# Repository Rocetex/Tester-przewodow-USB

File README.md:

# Tester przewodow USB
## Wstęp:
Jako projekt wstępnie wybrano tester przewodów USB. Wymagania przyjęte do tego projektu były następujące: stosunkowo niski koszt, prostota obsługi, kompaktowość i wszechstronność. Zdecydowano się, aby tester przeznaczony był dla przewodów USB type C - USB type C. Po podłączeniu przewodów do urządzenia  powinno ono podświetleniem poszczególnych diod ukazywać w jakim trybie może działać dany przewód, oraz możliwe uszkodzenia i cięcia budżetowe producenta w jego strukturze. 

## Założenia projektu:
* Możliwość testu 2 typów przewodów: USB A -> USB C oraz USB C -> USB C
* Dwa tryby częstotliwości pracy układu
* Kompaktowość urządzenia
* Niska cena
  
## Schemat i projekt układu
Wstępny zamysł projektu był następujący. Odpowiednio zaprojektowany system zegara CLK oparty o układ scalony NE555. Następnie sygnał ten przechodzi na 5 przerzutników typu JK działających w układzie licznika synchronicznego od 0 - 24, dzięki czemu możliwe było obsłużenie wszystkich 25 sygnałów pełnego złącza USB type C (a dokładniej 24 pinów sygnałowych oraz shielda). W ten sposób zaprojektowano układ licznika 5 bitowego. Sygnał z poszczególnych wyjść liczników trafia na dwa 4 bitowe dekodery połączone w odpowiedni sposób, zamiast na jeden dekoder 5 bitowy. Wynika to z faktu dostępności i ceny. Układ dwóch 4 bitowych dekoderów jest tańszy i łatwiej dostępny. Sygnał z poszczególnych wyjść dekoderów trafiał na odpowiednie mosfety typu P, a one po otrzymaniu sygnału załączeniowego (logiczne “0”) zaczynały przewodzić do odpowiedniego pinu złącza USB C. Następnie przez przewód sygnał trafiał na odpowiednie szeregowo połączone rezystory i diody, które zaczynały świecić, sygnalizująć działanie danego pinu.

## Instrukcja obsługi:
Płytkę należy zasilić napięciem 5V. 
Switch S1 odowiada za resetowanie układu.
Przełącznik S3 odpowiada za wybranie częstotliwości pracy układu
Przełącznik S4 odpowiada za wybranie trybu pracy:
1) USB typu A
2) USB typu C
Aby przetestować przewód USB A -> USB C:
- Podłączyć zasilanie do płytki
- Ustawić oczelowamą częstotliwość pracy układu
- Ustawić tryb pracy na USB A
- Wpiąć przewód z złącze USB A (oznaczone na płytce jako J3) oraz w wyjściowe złącze USB typu C (J2)
Aby przetestować przewód USB C -> USB C:
- Podłączyć zasilanie do płytki
- Ustawić oczelowamą częstotliwość pracy układu
- Ustawić tryb pracy na USB C
- Wpiąć przewód z złącze USB C (oznaczone na płytce jako J1) oraz w wyjściowe złącze USB typu C (J2)

## Błędy w konstrukcji płytki:
- Kondensator C3 należy przylutować równolegle do masy oraz do zwartych padów miejsca kondensatora
- Pomimo wykonania symulacji zauważono problem z zamykaniem się mosfetów, z tego powodu zaleca się użycie tranzystorów PNP oraz rezystorów na bramce 1k Ohm

## Prezentacja układu:

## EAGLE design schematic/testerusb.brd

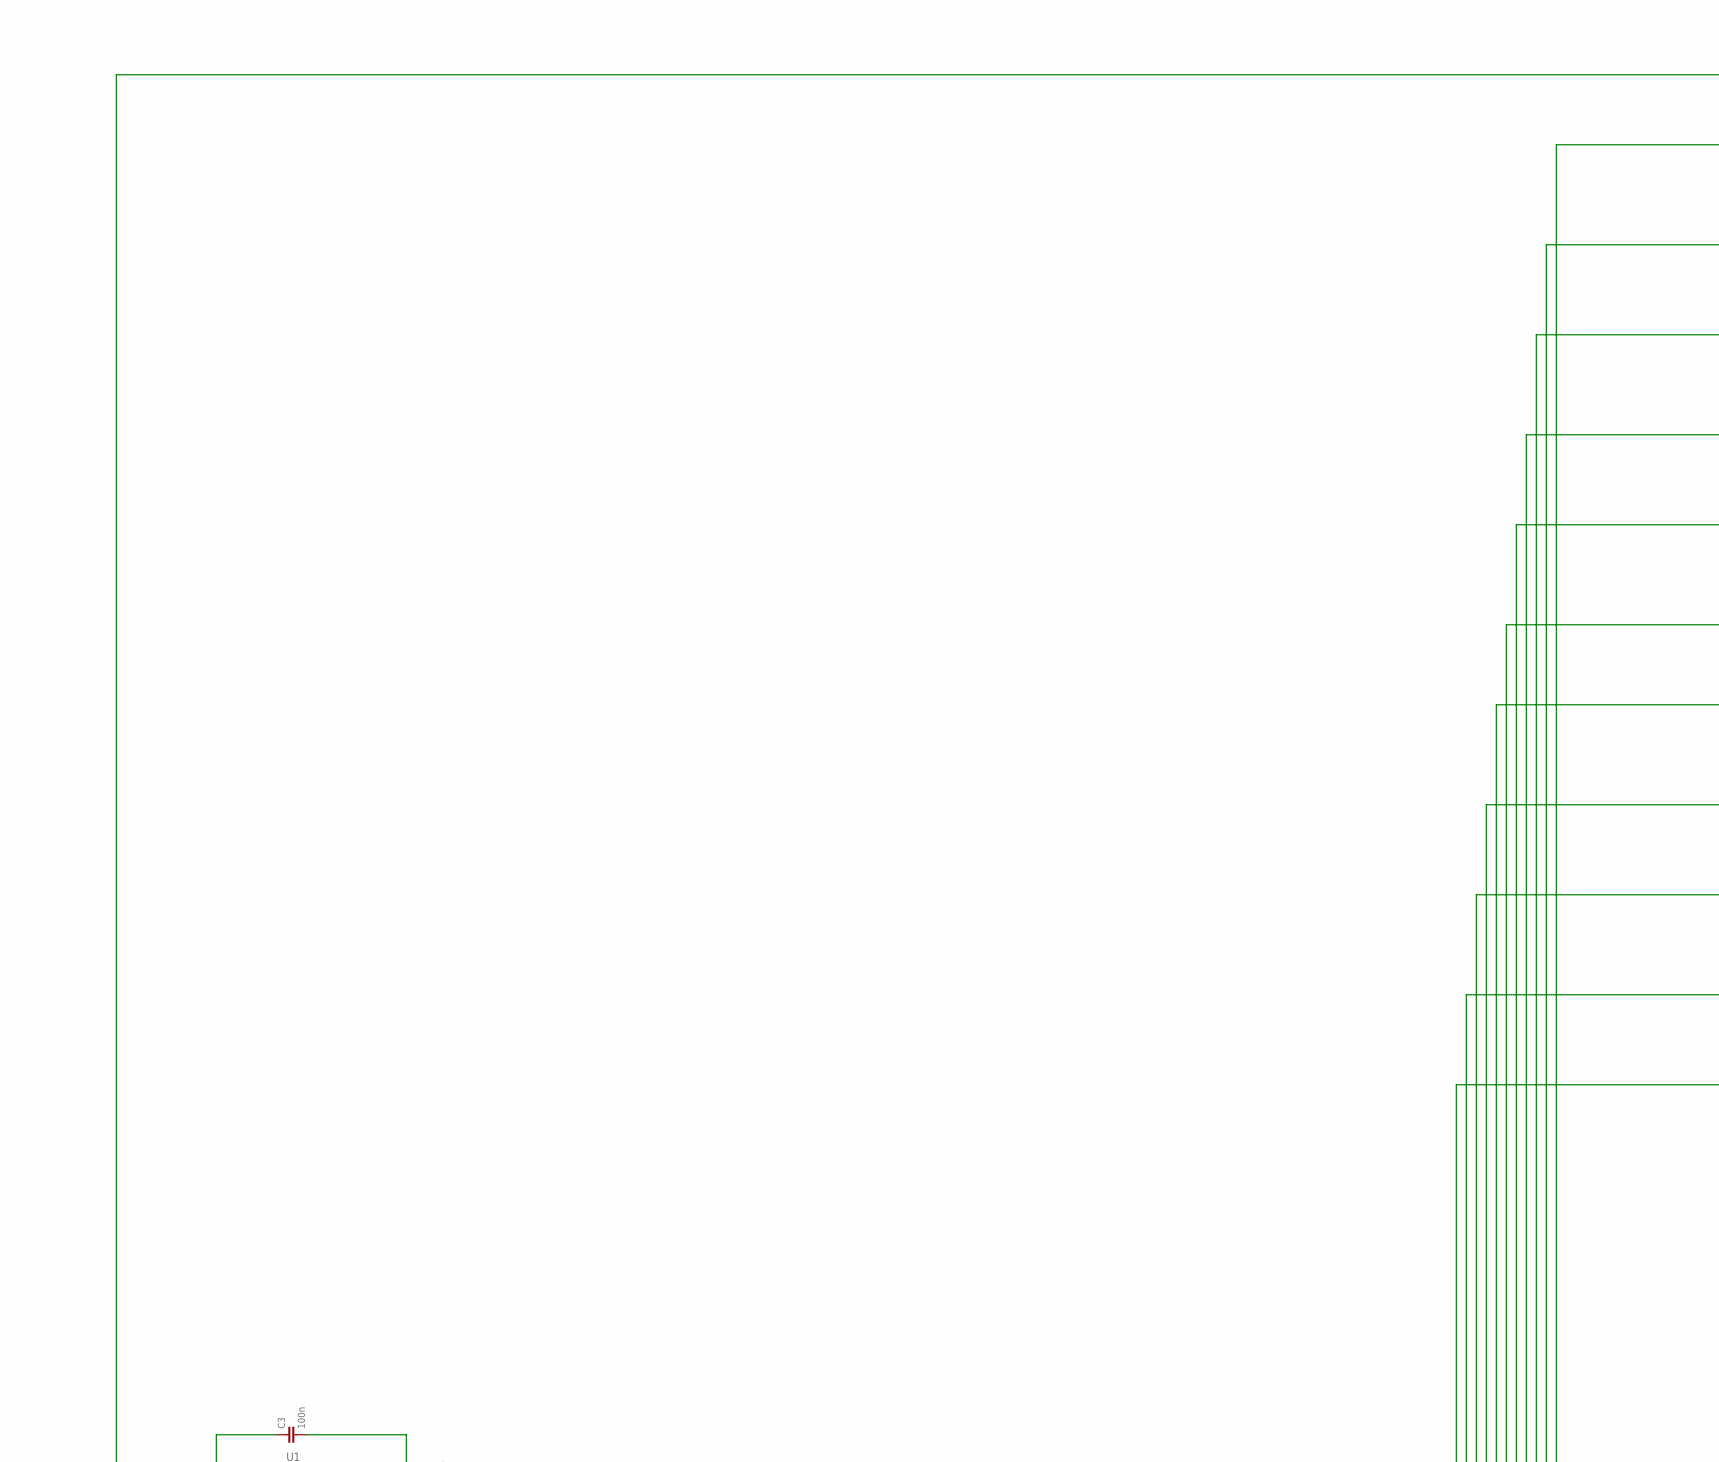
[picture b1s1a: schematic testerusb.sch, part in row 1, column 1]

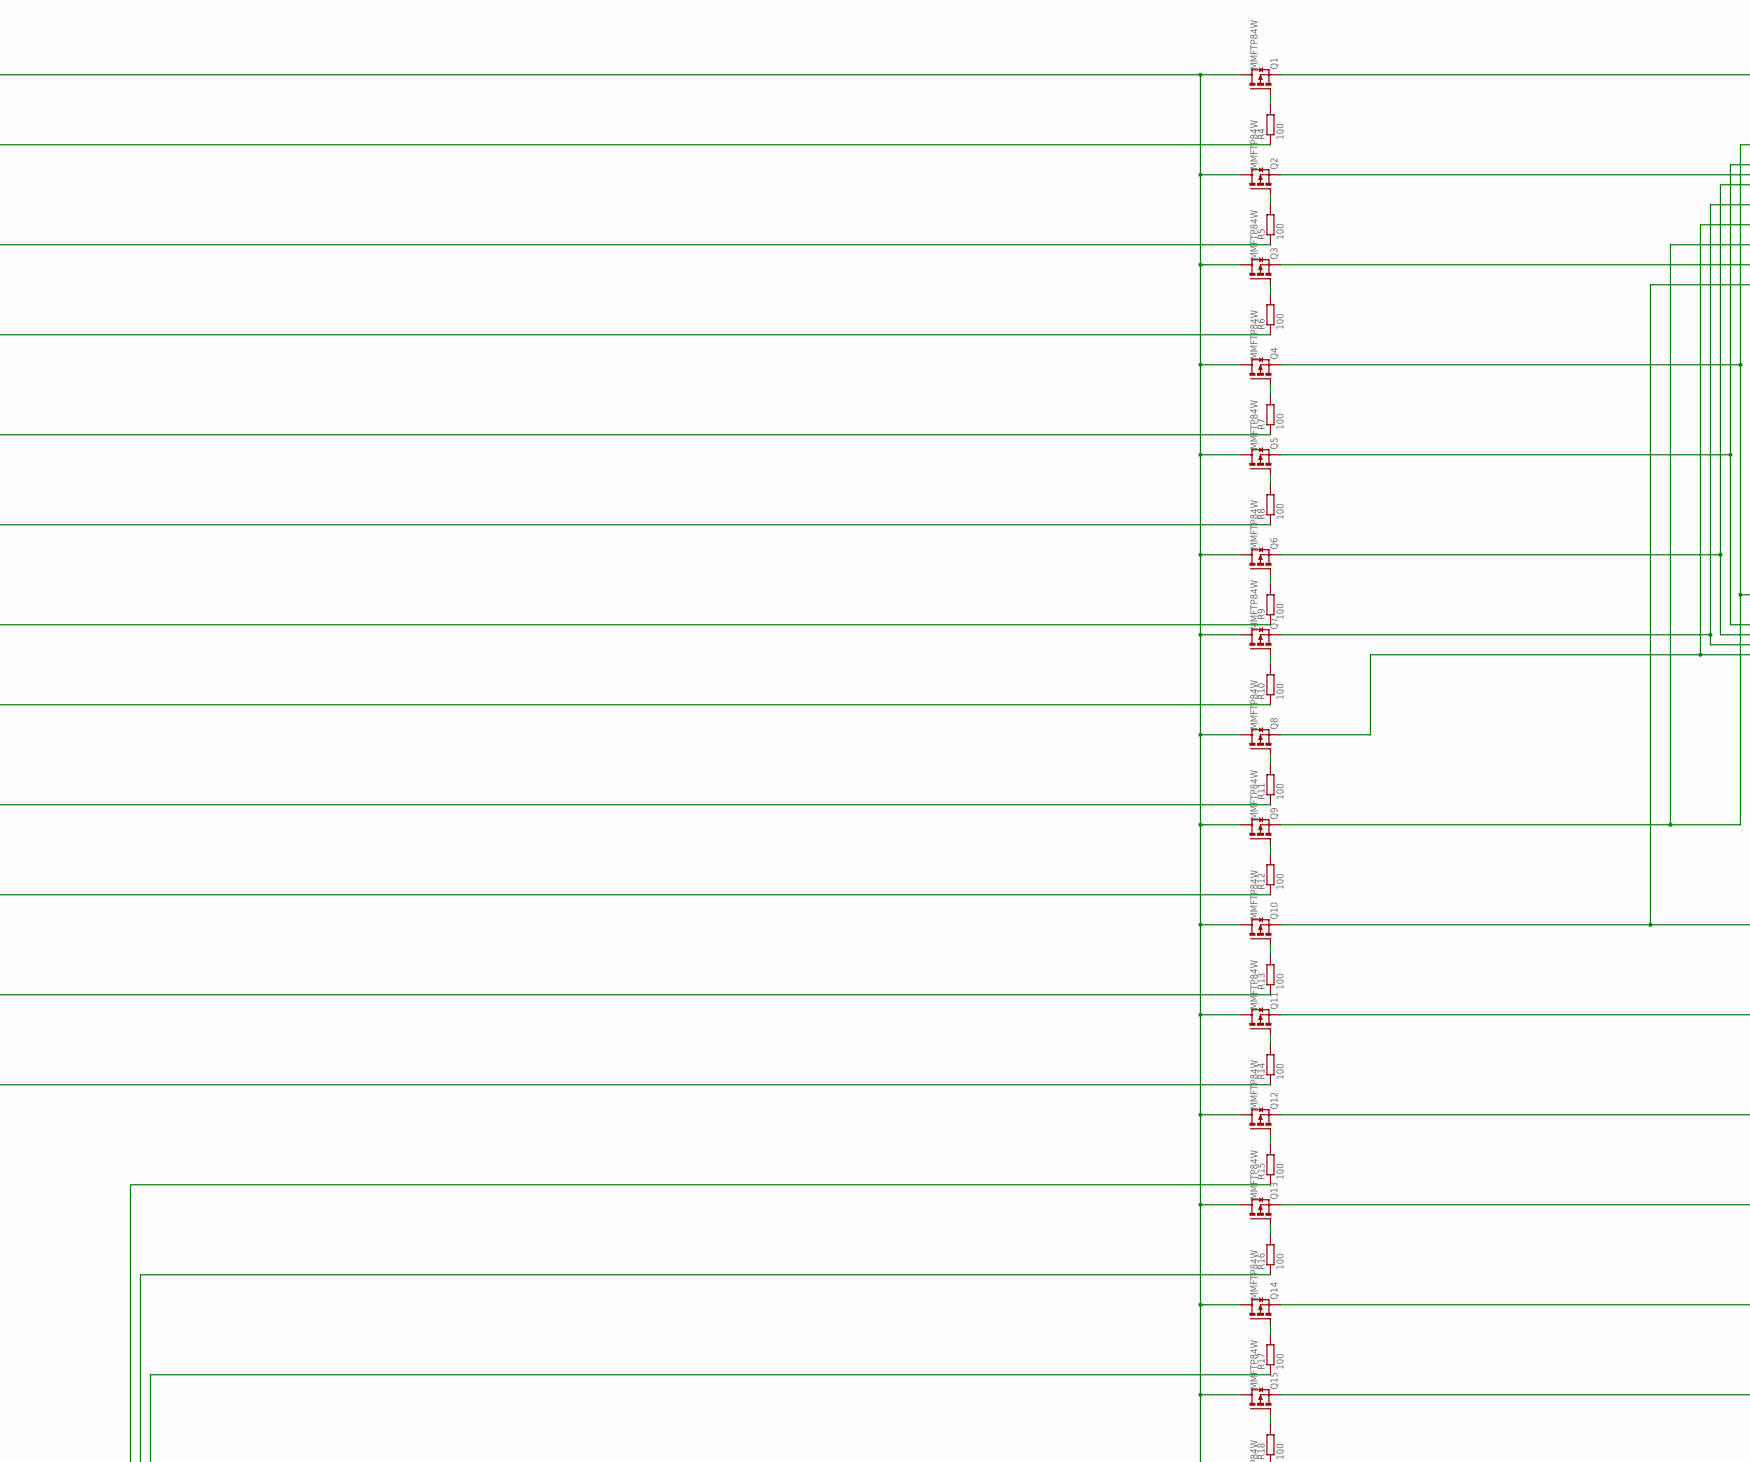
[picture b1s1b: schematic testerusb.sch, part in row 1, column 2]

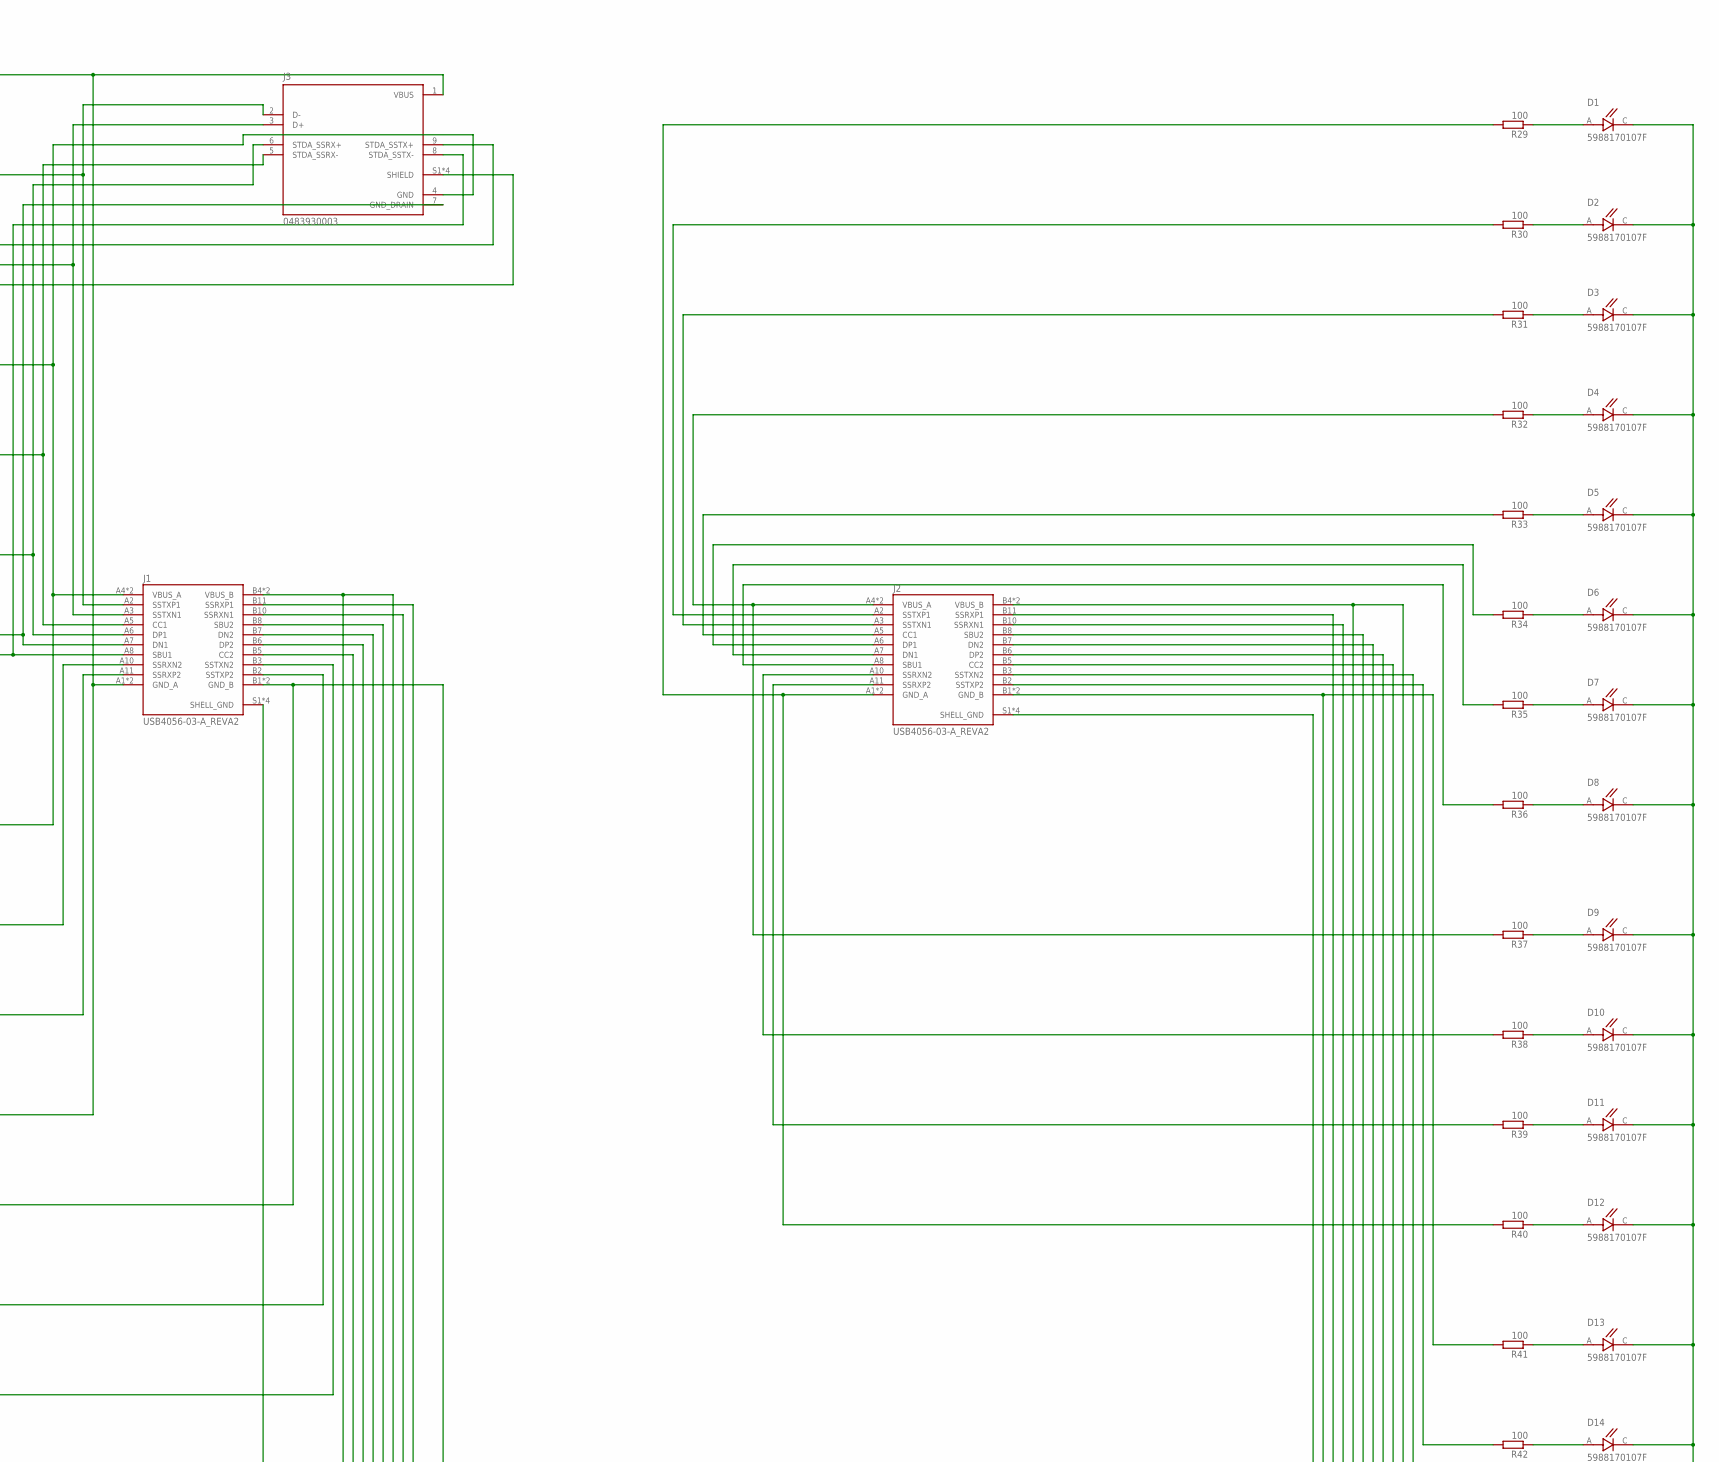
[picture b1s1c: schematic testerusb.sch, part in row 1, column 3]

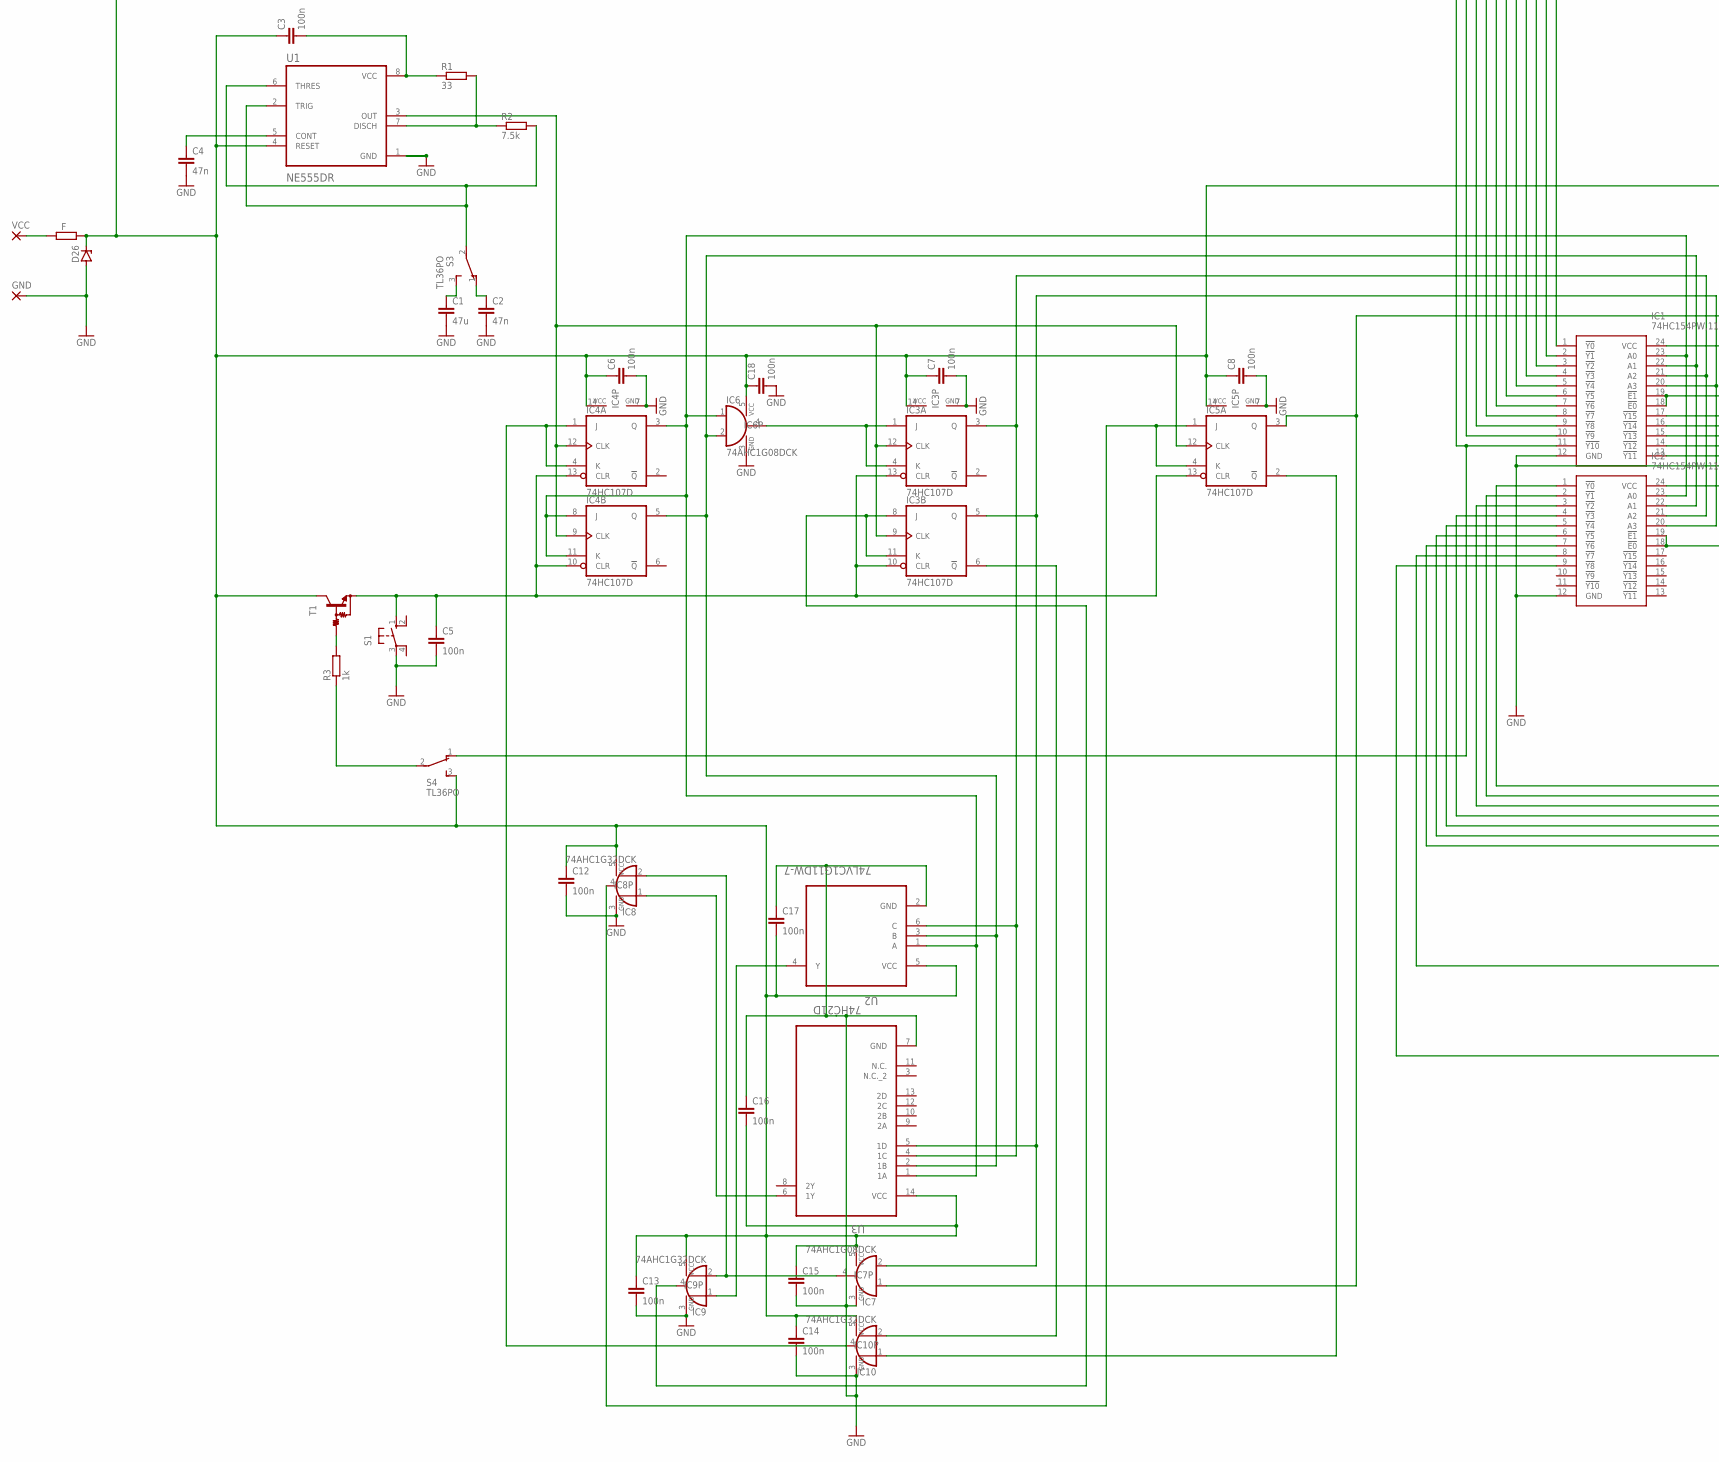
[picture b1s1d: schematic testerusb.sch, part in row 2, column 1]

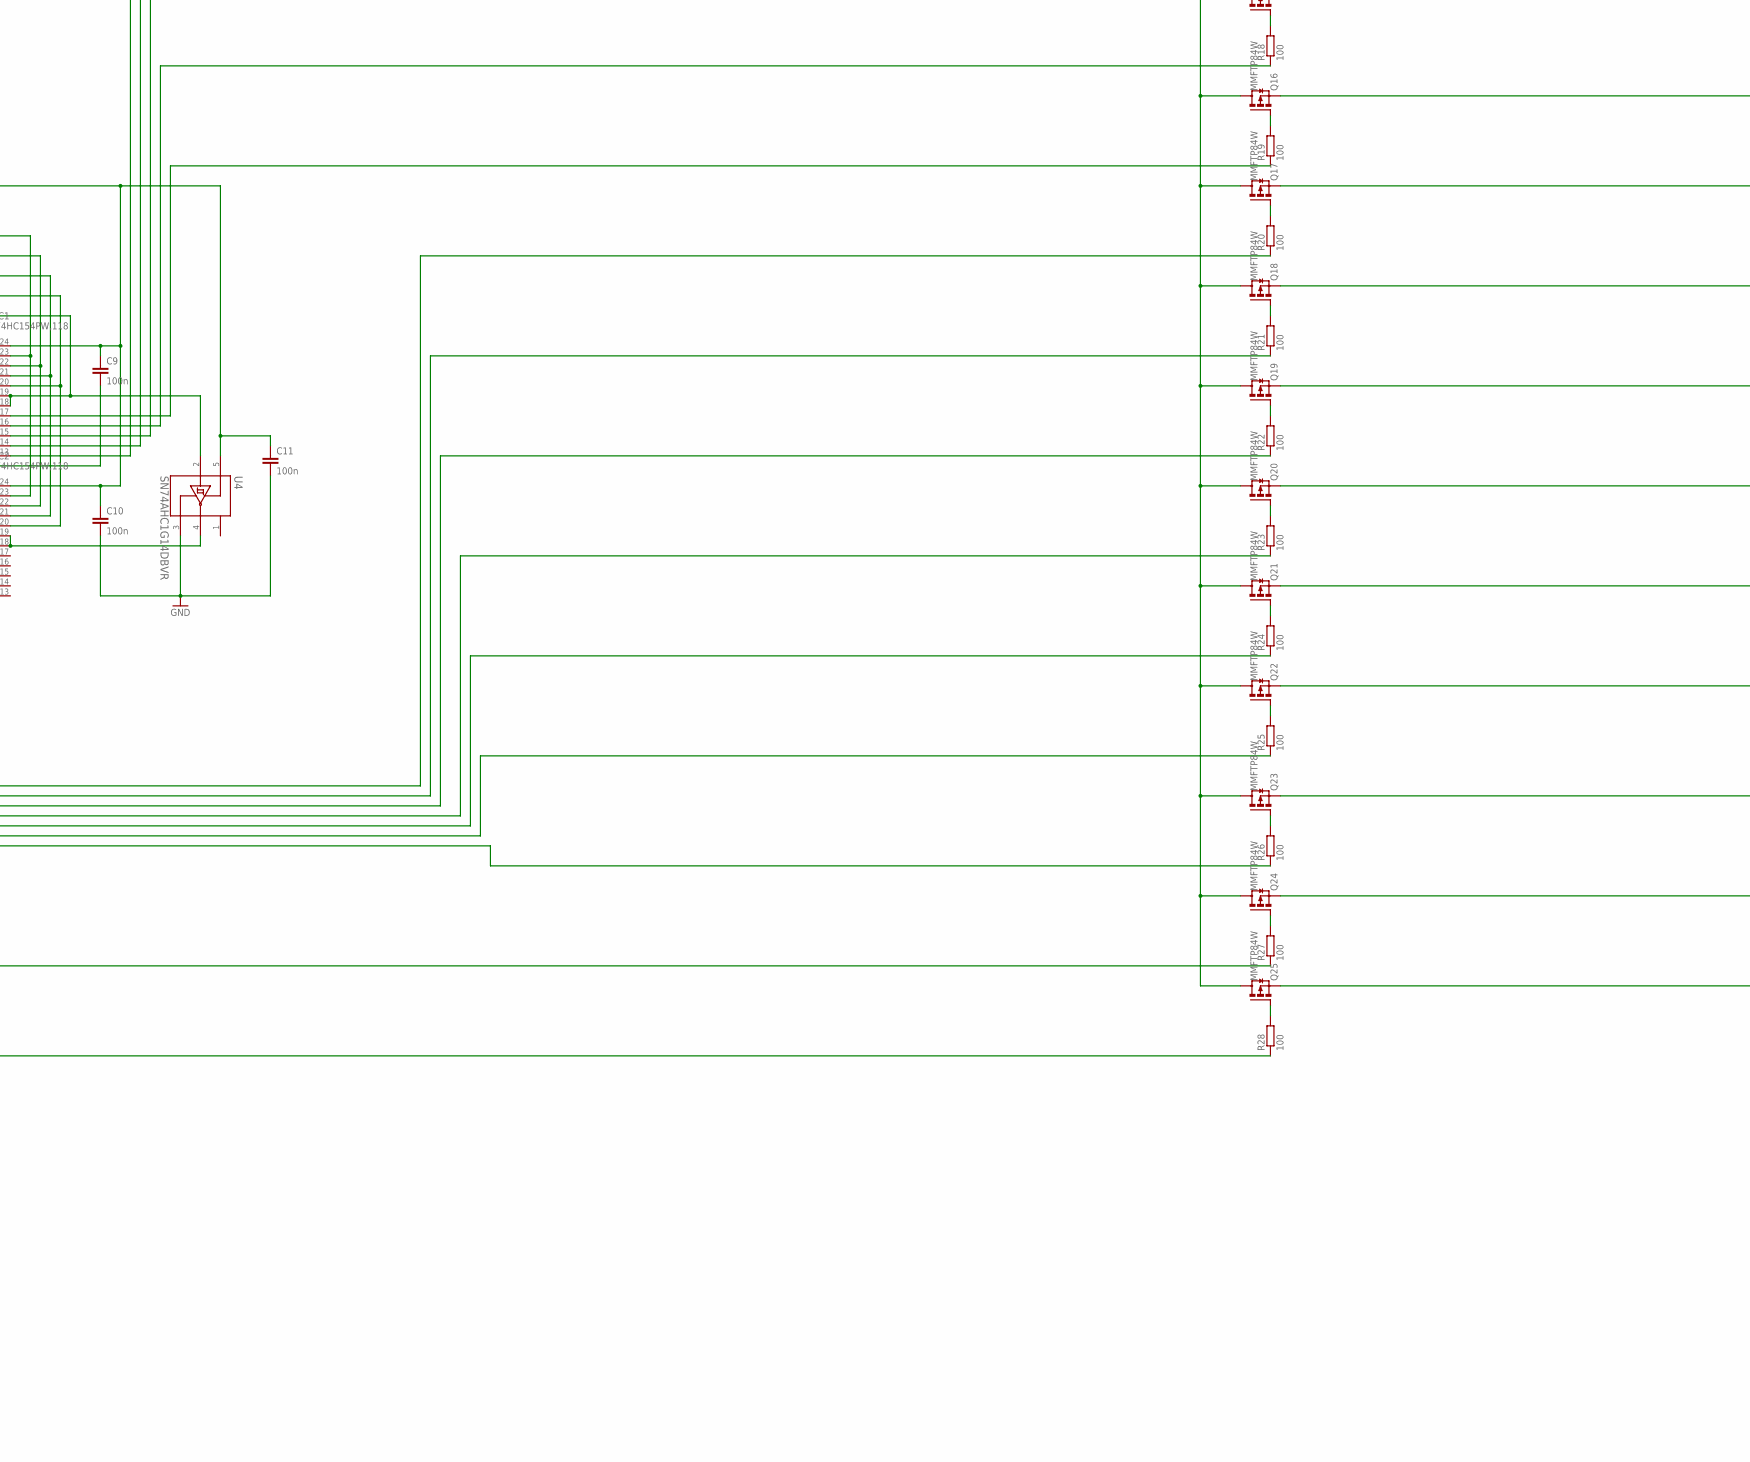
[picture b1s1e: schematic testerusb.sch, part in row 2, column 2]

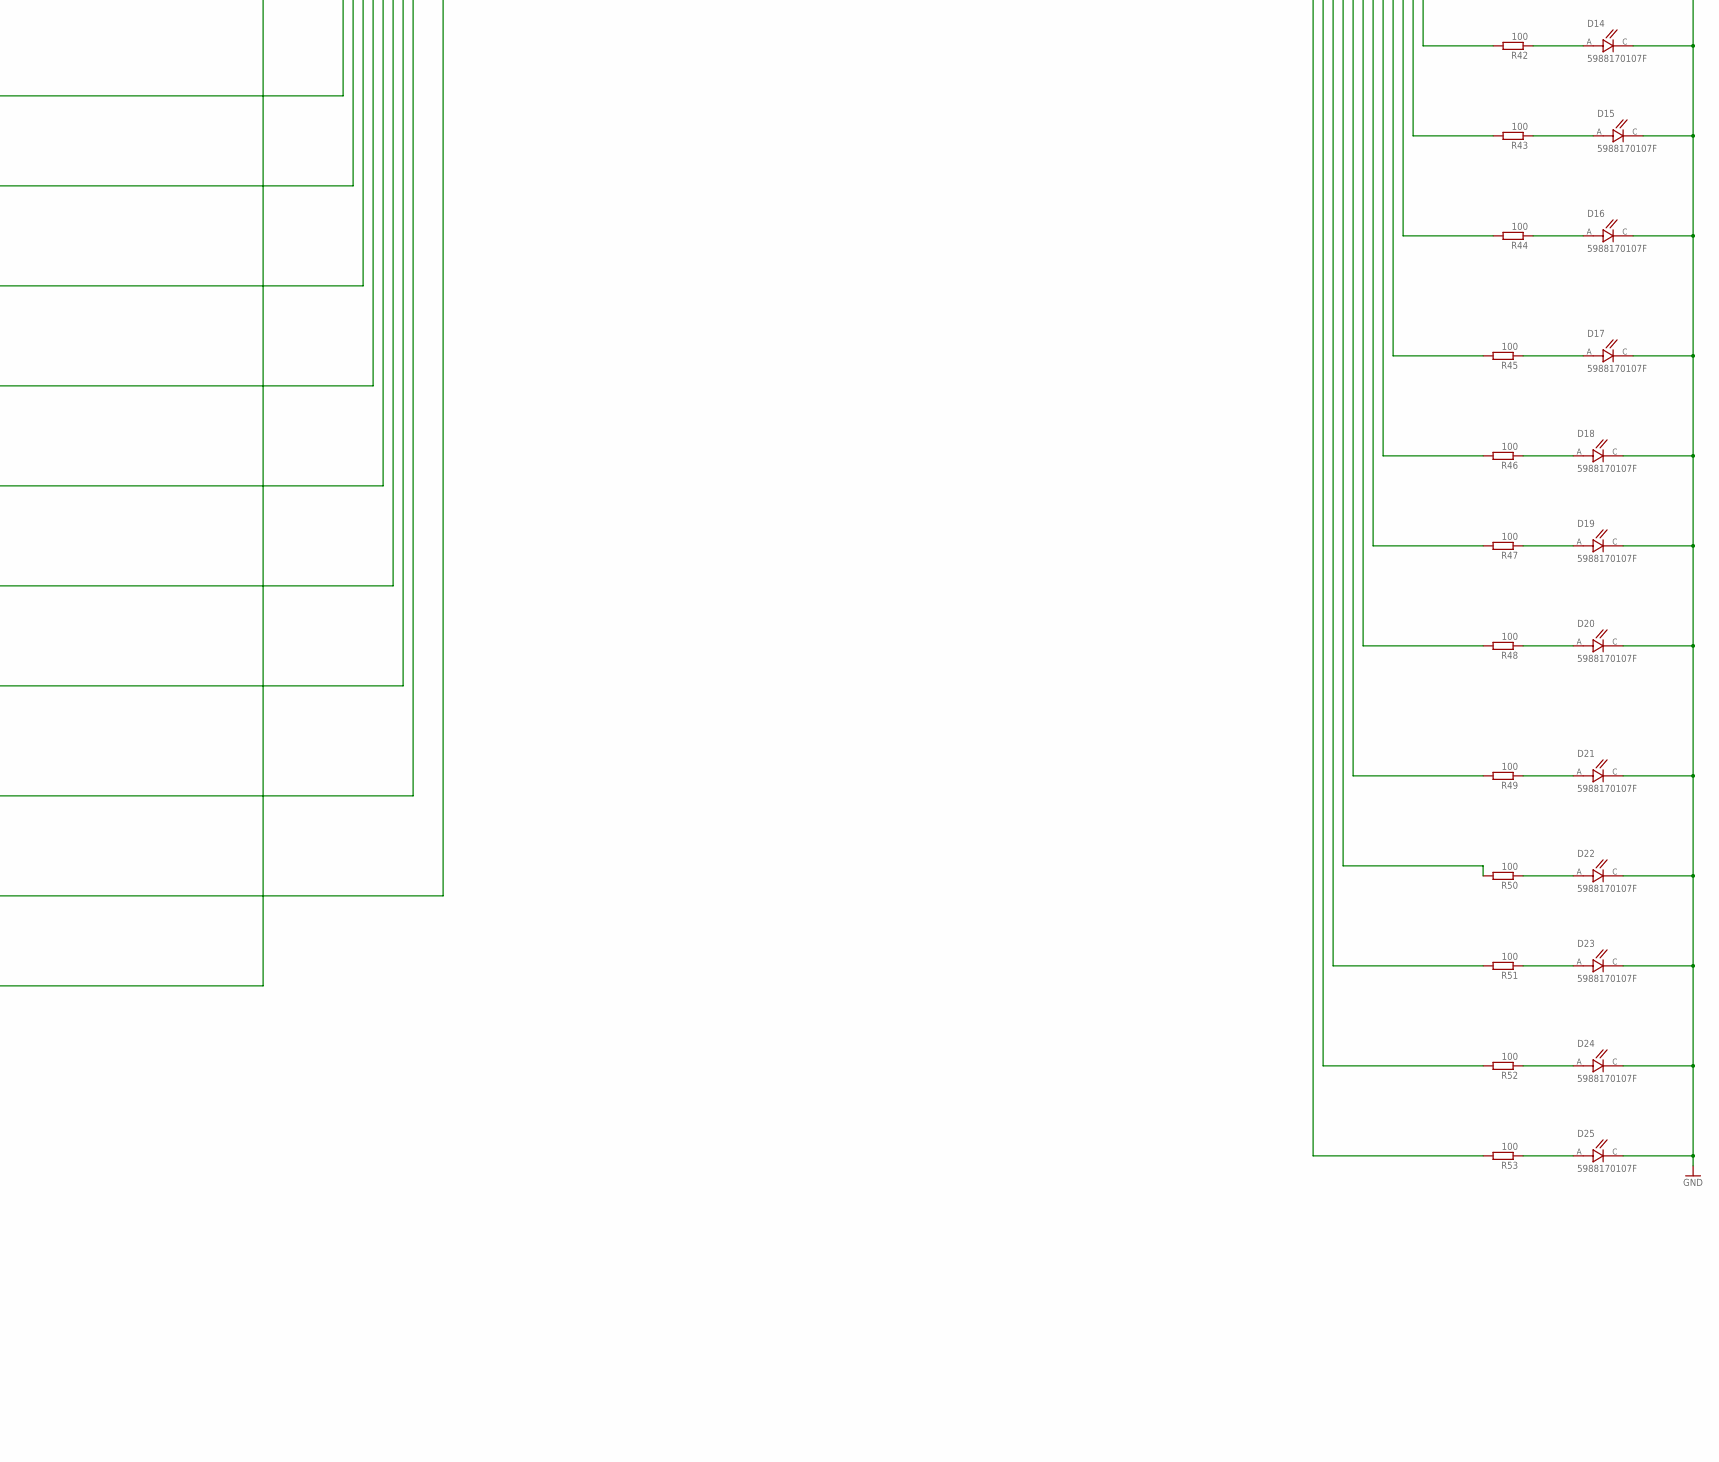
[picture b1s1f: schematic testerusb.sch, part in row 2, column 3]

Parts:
C1: 47u; C025_050-035X075
C2, C4: 47n; C025_050-035X075
C3, C5, C6, C7, C8, C9, C10, C11, C12, C13, C14, C15, C16, C17, C18: 100n; C0805
D1, D2, D3, D4, D5, D6, D7, D8, D9, D10, D11, D12, D13, D14, D15, D16, D17, D18, D19, D20, D21, D22, D23, D24, D25: 5988170107F; LEDC2012X70N
D26: ZENER-DIODEP1-12; P1Z12
F: R-EU_1812X7R; 1812X7R
GND: 3,81/1,4
IC1, IC2: 74HC154PW,118; SOP65P640X110-24N
IC3, IC4, IC5: 74HC107D; SO14
IC6, IC7: 74AHC1G08DCK; SC70-5
IC8, IC9, IC10: 74AHC1G32DCK; SC70-5
J1, J2: USB4056-03-A_REVA2; GCT_USB4056-03-A_REVA2
J3: 0483930003; MOLEX_0483930003
Q1, Q2, Q3, Q4, Q5, Q6, Q7, Q8, Q9, Q10, Q11, Q12, Q13, Q14, Q15, Q16, Q17, Q18, Q19, Q20, Q21, Q22, Q23, Q24, Q25: MMFTP84W; SUPER-SOT3
R1: 33; 0207/10
R2: 7.5k; 0207/10
R3: 1k; R0805
R4, R5, R6, R7, R8, R9, R10, R11, R12, R13, R14, R15, R16, R17, R18, R19, R20, R21, R22, R23, R24, R25, R26, R27, R28, R29, R30, R31, R32, R33, R34, R35, R36, R37, R38, R39, R40, R41, R42, R43, R44, R45, R46, R47, R48, R49, R50, R51, R52, R53: 100; R0805
S1: 10-XX; B3F-10XX
S3, S4: TL36PO; TL3XPO
T1: MUN2211T1-NPN_DRIVER-SC59-BEC; SC59-BEC
U1: NE555DR; SOIC127P599X175-8N
U2: 74LVC1G11DW-7; SOT65P210X110-6N
U3: 74HC21D; SOIC127P600X175-14N
U4: SN74AHC1G14DBVR; SOT95P280X145-5N
VCC: 3,81/1,4

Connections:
GND: C1.2, C2.2, C4.2, C5.2, C6.2, C7.2, C8.2, C9.2, C10.2, C11.2, C12.2, C13.2, C14.2, C15.2, C16.1, C17.1, C18.2, D1.C, D2.C, D3.C, D4.C, D5.C, D6.C, D7.C, D8.C, D9.C, D10.C, D11.C, D12.C, D13.C, D14.C, D15.C, D16.C, D17.C, D18.C, D19.C, D20.C, D21.C, D22.C, D23.C, D24.C, D25.C, D26.A, GND.1, IC1.12 (GND), IC2.12 (GND), IC3.7 (GND), IC4.7 (GND), IC5.7 (GND), IC6.3 (GND), IC7.3 (GND), IC8.3 (GND), IC9.3 (GND), IC10.3 (GND), S1.3, U1.1 (GND), U2.2 (GND), U3.7 (GND), U4.3 (GND)
unnamed: Q1.1 (G), R4.2
unnamed: Q2.1 (G), R5.2
unnamed: IC4.1 (J), IC4.4 (K), IC10.4 (O)
unnamed: IC1.18 (!E0), IC1.19 (!E1), IC5.3 (Q), IC7.1 (I0), U4.2 (A)
unnamed: IC3.1 (J), IC3.4 (K), IC6.4 (O)
unnamed: IC3.8 (J), IC3.11 (K), IC9.4 (O)
unnamed: IC5.1 (J), IC5.4 (K), IC8.4 (O)
unnamed: F.1, VCC.1
unnamed: C1.1, S3.3 (S)
unnamed: C3.2, R1.1, U1.8 (VCC)
unnamed: C3.1, C6.1, C7.1, C8.1, C9.1, C10.1, C11.1, C12.1, C13.1, C14.1, C15.1, C16.2, C17.2, C18.1, D26.C, F.2, IC1.24 (VCC), IC2.24 (VCC), IC3.14 (VCC), IC4.14 (VCC), IC5.14 (VCC), IC6.5 (VCC), IC7.5 (VCC), IC8.5 (VCC), IC9.5 (VCC), IC10.5 (VCC), Q1.3 (D), Q2.3 (D), Q3.3 (D), Q4.3 (D), Q5.3 (D), Q6.3 (D), Q7.3 (D), Q8.3 (D), Q9.3 (D), Q10.3 (D), Q11.3 (D), Q12.3 (D), Q13.3 (D), Q14.3 (D), Q15.3 (D), Q16.3 (D), Q17.3 (D), Q18.3 (D), Q19.3 (D), Q20.3 (D), Q21.3 (D), Q22.3 (D), Q23.3 (D), Q24.3 (D), Q25.3 (D), S4.3 (S), T1.C, U1.4 (RESET), U2.5 (VCC), U3.14 (VCC), U4.5 (VCC)
unnamed: R1.2, R2.1, U1.7 (DISCH)
unnamed: C4.1, U1.5 (CONT)
unnamed: C2.1, S3.1 (O)
unnamed: R2.2, S3.2, U1.2 (TRIG), U1.6 (THRES)
unnamed: IC3.9 (CLK), IC3.12 (CLK), IC4.9 (CLK), IC4.12 (CLK), IC5.12 (CLK), U1.3 (OUT)
unnamed: R3.2, T1.B
unnamed: C5.1, IC3.10 (CLR), IC3.13 (CLR), IC4.10 (CLR), IC4.13 (CLR), IC5.13 (CLR), S1.1 (S), T1.E
unnamed: IC1.2 (!Y1), R5.1
unnamed: R3.1, S4.2
unnamed: IC1.11 (!Y10), R14.1, S4.1 (O)
unnamed: IC3.6 (!Q), IC10.2 (I1)
unnamed: IC1.22 (A1), IC2.22 (A1), IC4.5 (Q), IC6.2 (I1), U2.3 (B), U3.2 (1B)
unnamed: IC1.23 (A0), IC2.23 (A0), IC4.3 (Q), IC4.8 (J), IC4.11 (K), IC6.1 (I0), U2.1 (A), U3.1 (1A)
unnamed: IC2.18 (!E0), IC2.19 (!E1), U4.4 (Y)
unnamed: IC5.2 (!Q), IC10.1 (I0)
unnamed: IC7.4 (O), IC8.2 (I1), IC9.2 (I1)
unnamed: IC9.1 (I0), U2.4 (Y)
unnamed: IC1.21 (A2), IC2.21 (A2), IC3.3 (Q), U2.6 (C), U3.4 (1C)
unnamed: IC1.20 (A3), IC2.20 (A3), IC3.5 (Q), IC7.2 (I1), U3.5 (1D)
unnamed: IC8.1 (I0), U3.6 (1Y)
unnamed: IC1.1 (!Y0), R4.1
unnamed: IC1.3 (!Y2), R6.1
unnamed: IC1.4 (!Y3), R7.1
unnamed: IC1.5 (!Y4), R8.1
unnamed: IC1.6 (!Y5), R9.1
unnamed: IC1.7 (!Y6), R10.1
unnamed: IC1.8 (!Y7), R11.1
unnamed: IC1.9 (!Y8), R12.1
unnamed: IC1.10 (!Y9), R13.1
unnamed: IC1.13 (!Y11), R15.1
unnamed: IC1.14 (!Y12), R16.1
unnamed: IC1.15 (!Y13), R17.1
unnamed: IC1.16 (!Y14), R18.1
unnamed: IC1.17 (!Y15), R19.1
unnamed: IC2.1 (!Y0), R20.1
unnamed: IC2.9 (!Y8), R28.1
unnamed: IC2.2 (!Y1), R21.1
unnamed: IC2.3 (!Y2), R22.1
unnamed: IC2.4 (!Y3), R23.1
unnamed: IC2.5 (!Y4), R24.1
unnamed: IC2.6 (!Y5), R25.1
unnamed: IC2.7 (!Y6), R26.1
unnamed: IC2.8 (!Y7), R27.1
unnamed: Q3.1 (G), R6.2
unnamed: Q4.1 (G), R7.2
unnamed: Q5.1 (G), R8.2
unnamed: Q6.1 (G), R9.2
unnamed: Q7.1 (G), R10.2
unnamed: Q8.1 (G), R11.2
unnamed: Q9.1 (G), R12.2
unnamed: Q10.1 (G), R13.2
unnamed: Q11.1 (G), R14.2
unnamed: Q12.1 (G), R15.2
unnamed: Q13.1 (G), R16.2
unnamed: Q14.1 (G), R17.2
unnamed: Q15.1 (G), R18.2
unnamed: Q16.1 (G), R19.2
unnamed: Q17.1 (G), R20.2
unnamed: Q18.1 (G), R21.2
unnamed: Q19.1 (G), R22.2
unnamed: Q20.1 (G), R23.2
unnamed: Q21.1 (G), R24.2
unnamed: Q22.1 (G), R25.2
unnamed: Q23.1 (G), R26.2
unnamed: Q24.1 (G), R27.2
unnamed: Q25.1 (G), R28.2
unnamed: D1.A, R29.1
unnamed: J1.A1 (GND_A), J1.A12 (GND_A), J3.1 (VBUS), Q1.2 (S), Q12.2 (S)
unnamed: J1.B1 (GND_B), J1.B12 (GND_B), Q13.2 (S), Q24.2 (S)
unnamed: J1.A2 (SSTXP1), J3.2 (D-), Q2.2 (S)
unnamed: J1.A3 (SSTXN1), J3.3 (D+), Q3.2 (S)
unnamed: J1.A4 (VBUS_A), J1.A9 (VBUS_A), J3.4 (GND), J3.9 (STDA_SSTX+), Q4.2 (S), Q9.2 (S)
unnamed: J1.A5 (CC1), J3.5 (STDA_SSRX-), Q5.2 (S)
unnamed: J1.A6 (DP1), J3.6 (STDA_SSRX+), Q6.2 (S)
unnamed: J1.A7 (DN1), J3.7 (GND_DRAIN), Q7.2 (S)
unnamed: J1.A8 (SBU1), J3.8 (STDA_SSTX-), Q8.2 (S)
unnamed: J1.A10 (SSRXN2), J3.S1 (SHIELD), J3.S2 (SHIELD), J3.S3 (SHIELD), J3.S4 (SHIELD), Q10.2 (S)
unnamed: J1.A11 (SSRXP2), Q11.2 (S)
unnamed: J1.B2 (SSTXP2), Q14.2 (S)
unnamed: J1.B3 (SSTXN2), Q15.2 (S)
unnamed: J1.B4 (VBUS_B), J1.B9 (VBUS_B), Q16.2 (S), Q21.2 (S)
unnamed: J1.B5 (CC2), Q17.2 (S)
unnamed: J1.B6 (DP2), Q18.2 (S)
unnamed: J1.B7 (DN2), Q19.2 (S)
unnamed: J1.B8 (SBU2), Q20.2 (S)
unnamed: D2.A, R30.1
unnamed: J1.B10 (SSRXN1), Q22.2 (S)
unnamed: J1.B11 (SSRXP1), Q23.2 (S)
unnamed: D3.A, R31.1
unnamed: J1.S1 (SHELL_GND), J1.S2 (SHELL_GND), J1.S3 (SHELL_GND), J1.S4 (SHELL_GND), Q25.2 (S)
unnamed: D4.A, R32.1
unnamed: D5.A, R33.1
unnamed: D6.A, R34.1
unnamed: D7.A, R35.1
unnamed: D8.A, R36.1
unnamed: D9.A, R37.1
unnamed: D10.A, R38.1
unnamed: D11.A, R39.1
unnamed: D12.A, R40.1
unnamed: D13.A, R41.1
unnamed: D14.A, R42.1
unnamed: D15.A, R43.1
unnamed: D16.A, R44.1
unnamed: D17.A, R45.1
unnamed: D18.A, R46.1
unnamed: D19.A, R47.1
unnamed: D20.A, R48.1
unnamed: D21.A, R49.1
unnamed: D22.A, R50.1
unnamed: D23.A, R51.1
unnamed: D24.A, R52.1
unnamed: D25.A, R53.1
unnamed: J2.A1 (GND_A), J2.A12 (GND_A), R29.2, R40.2
unnamed: J2.A2 (SSTXP1), R30.2
unnamed: J2.A3 (SSTXN1), R31.2
unnamed: J2.A4 (VBUS_A), J2.A9 (VBUS_A), R32.2, R37.2
unnamed: J2.A5 (CC1), R33.2
unnamed: J2.A6 (DP1), R34.2
unnamed: J2.A7 (DN1), R35.2
unnamed: J2.A8 (SBU1), R36.2
unnamed: J2.A10 (SSRXN2), R38.2
unnamed: J2.A11 (SSRXP2), R39.2
unnamed: J2.B1 (GND_B), J2.B12 (GND_B), R41.2, R52.2
unnamed: J2.B2 (SSTXP2), R42.2
unnamed: J2.B3 (SSTXN2), R43.2
unnamed: J2.B4 (VBUS_B), J2.B9 (VBUS_B), R44.2, R49.2
unnamed: J2.B5 (CC2), R45.2
unnamed: J2.B6 (DP2), R46.2
unnamed: J2.B7 (DN2), R47.2
unnamed: J2.B8 (SBU2), R48.2
unnamed: J2.B10 (SSRXN1), R50.2
unnamed: J2.B11 (SSRXP1), R51.2
unnamed: J2.S1 (SHELL_GND), J2.S2 (SHELL_GND), J2.S3 (SHELL_GND), J2.S4 (SHELL_GND), R53.2
